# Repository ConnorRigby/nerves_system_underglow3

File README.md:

# ConeRGB Underglow3 Nerves Support

This is the base Nerves System configuration for [ConeRGB V3](https://github.com/connorrigby/underglow3).

| Feature              | Description                     |
| -------------------- | ------------------------------- |
| CPU                  | 1.2 GHz ARM Cortex-A7 Dual-Core |
| Memory               | 128 MB DDR3                     |
| Storage              | MicroSD                         |
| Linux kernel         | 6.1 w/ patches                  |
| IEx terminal         | UART `ttyS0`                    |
| GPIO, I2C, SPI       | Yes - [Elixir Circuits](https://github.com/elixir-circuits) |
| Display              | No                              |
| ADC                  | No                              |
| PWM                  | 8 channels                      |
| UART                 | ttyS0                           |
| Camera               | No                              |
| Ethernet             | No                              |
| WiFi                 | Onboard WiFi                    |
| RTC                  | No                              |
| HW Watchdog          | Yes                             |

## Special Thanks

Most of the hard work in this repo was gleamed from [YuzukiSBC](https://github.com/YuzukiHD/Buildroot-YuzukiSBC)

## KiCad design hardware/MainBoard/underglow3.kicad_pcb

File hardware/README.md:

# v0.1.0 RELEASE

This directory contains a tagged version of the "real" hardware repo. 
Everything in this directory should be considered for reference only and not used as source directly.

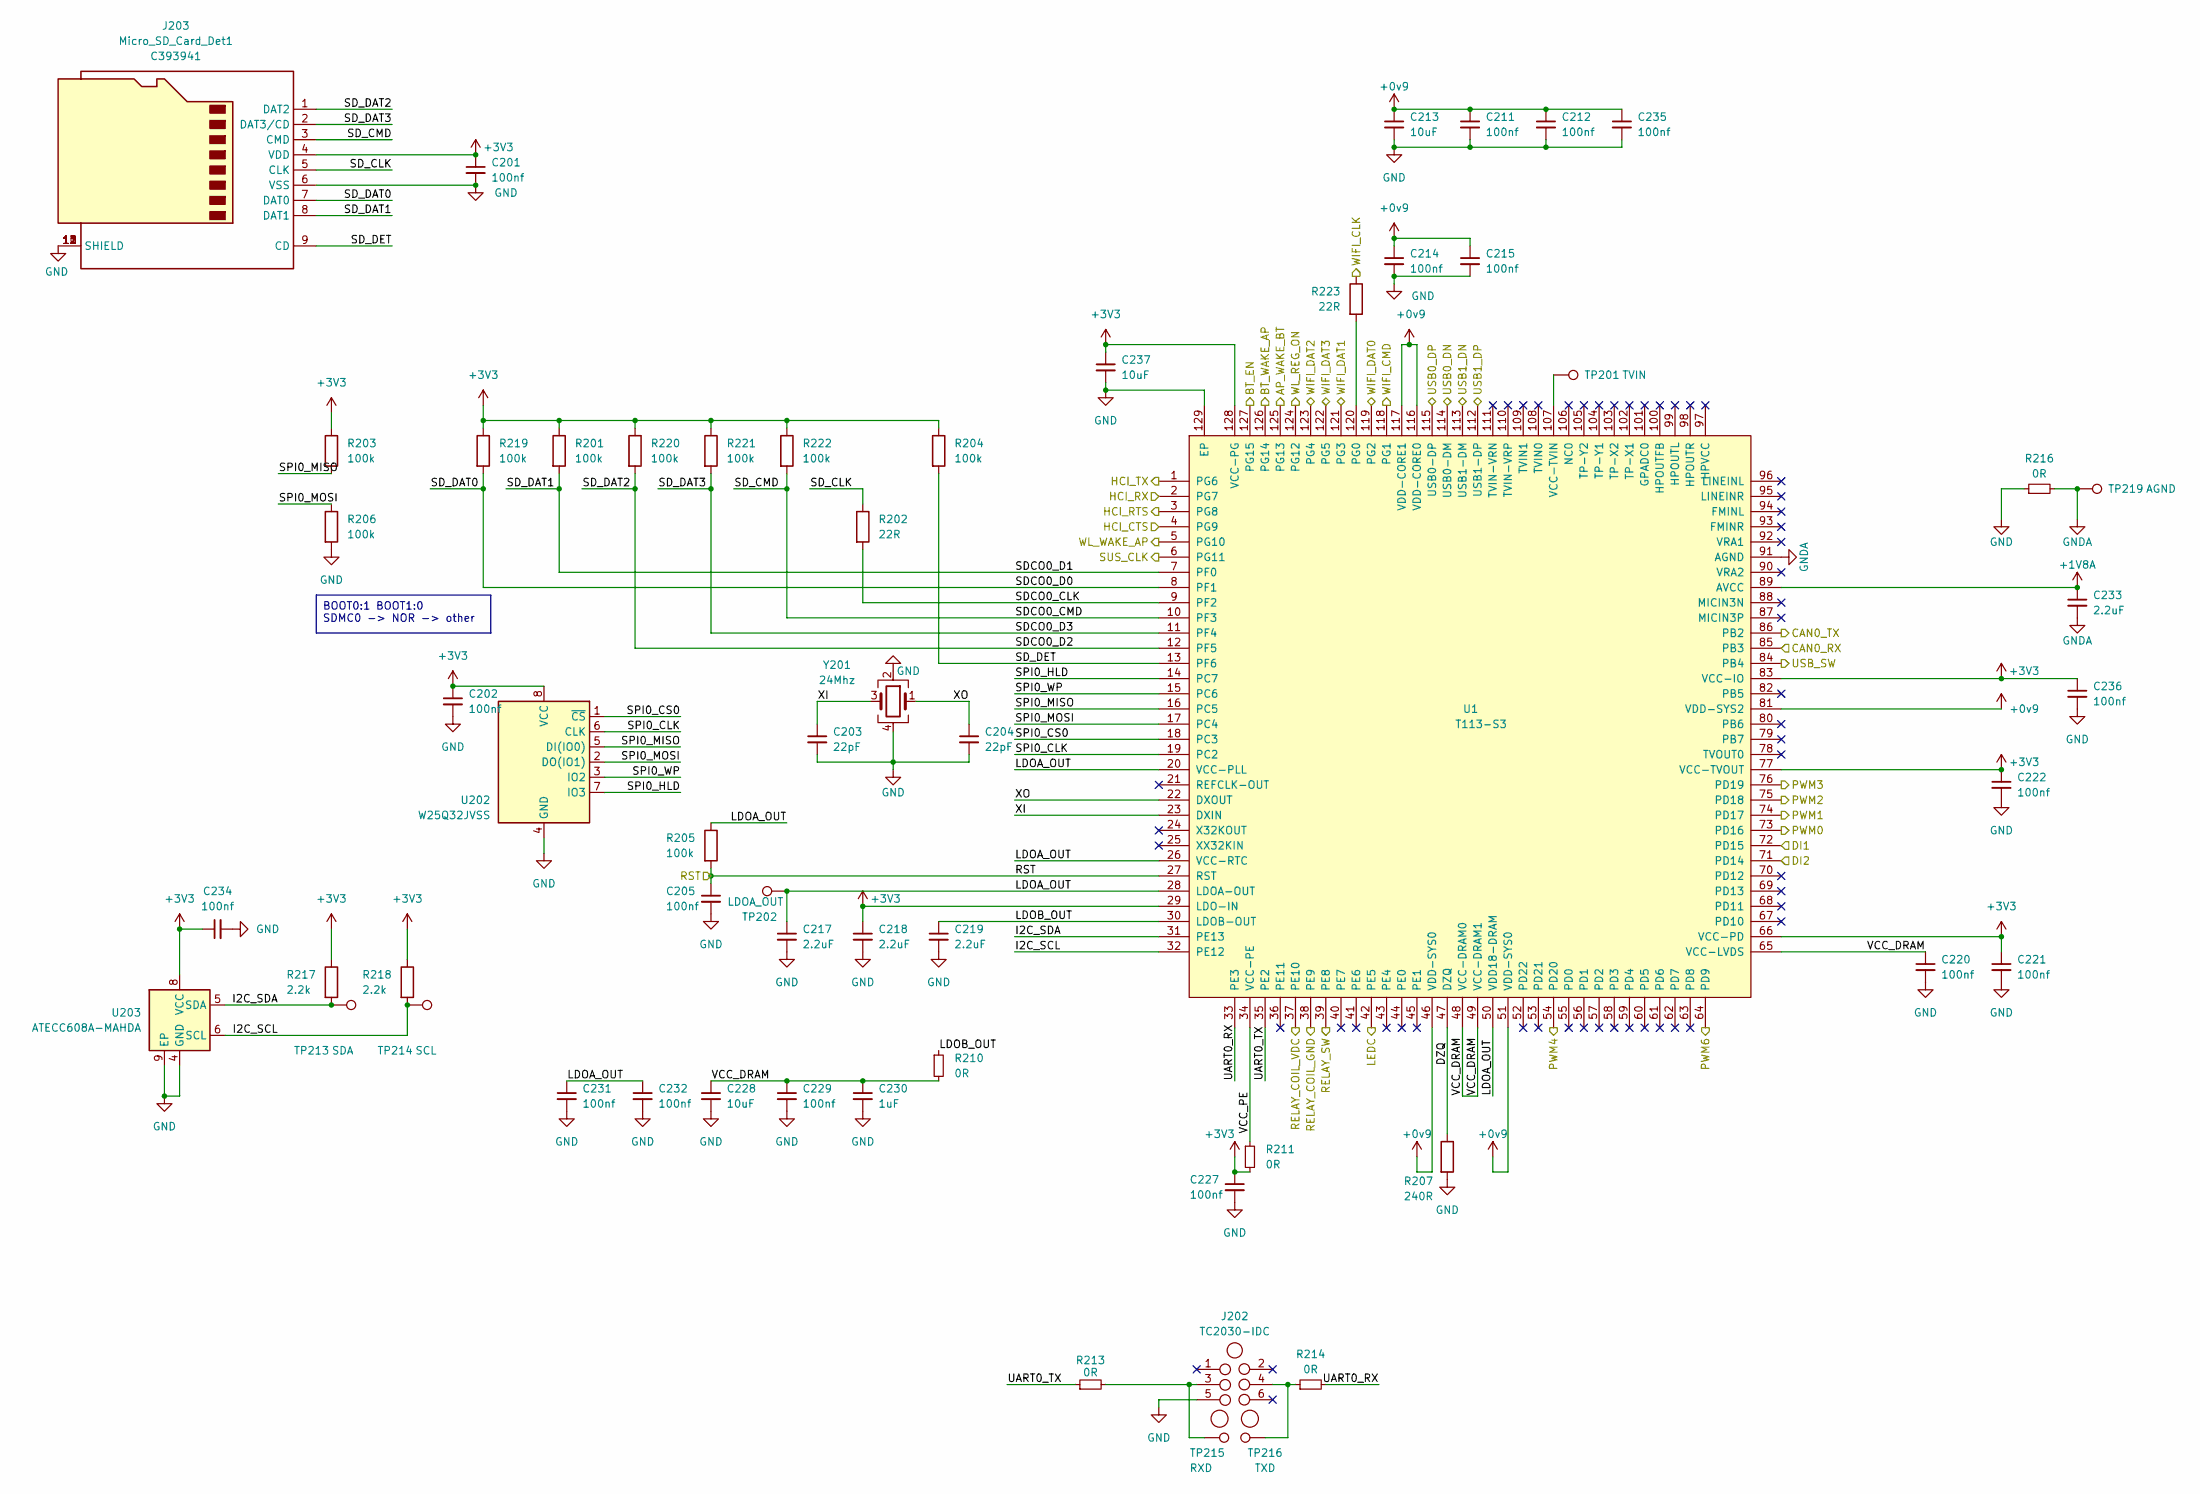
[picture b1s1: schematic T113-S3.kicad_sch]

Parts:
C201, C202, C205, C211, C212, C214, C215, C220, C221, C222, C227, C229, C231, C232, C234, C235, C236: 100nf; C_0402_1005Metric; MPN CL05B104KB54PNC; LCSC C307331
C203, C204: 22pF; C_0402_1005Metric; MPN 0402CG220J500NT; LCSC C1555
C213, C228, C237: 10uF; C_0603_1608Metric; MPN CL10A106MA8NRNC; LCSC C96446
C217, C218, C219, C233: 2.2uF; R_0402_1005Metric; MPN CL05A225MQ5NSNC; LCSC C12530
C230: 1uF; R_0402_1005Metric; MPN CL05A105KA5NQNC; LCSC C52923
J202: TC2030-IDC; Tag-Connect_TC2030-IDC-NL_2x03_P1.27mm_Vertical
J203: Micro_SD_Card_Det1; TF-SMD_TF-PUSH; MPN TF PUSH; LCSC C393941
R201, R203, R204, R205, R206, R219, R220, R221, R222: 100k; R_0402_1005Metric; MPN 0402WGF1003TCE; LCSC C25741
R202, R223: 22R; R_0402_1005Metric; MPN 0402WGF220JTCE; LCSC C25092
R207: 240R; R_0402_1005Metric; MPN 0402WGF2400TCE; LCSC C25094
R210, R211, R213, R214, R216: 0R; R_0402_1005Metric; MPN 0402WGF0000TCE; LCSC C17168
R217, R218: 2.2k; R_0402_1005Metric; MPN 0603WAF2201T5E; LCSC C4190
TP201: TVIN; TestPoint_Pad_D1.0mm
TP202: LDOA_OUT; TestPoint_Pad_D1.0mm
TP213: SDA; TestPoint_Pad_D1.0mm
TP214: SCL; TestPoint_Pad_D1.0mm
TP215: RXD; TestPoint_Pad_D1.0mm
TP216: TXD; TestPoint_Pad_D1.0mm
TP219: AGND; TestPoint_Pad_D1.0mm
U1: T113-S3; LQFP-128_L14.0-W14.0-P0.40-LS16.0-BL-EP5.6; MPN T113-S3; LCSC C5197687
U202: W25Q32JVSS; SOIC-8_5.23x5.23mm_P1.27mm; MPN W25Q32JVSSIQ; LCSC C179173
U203: ATECC608A-MAHDA; DFN-8-1EP_3x2mm_P0.5mm_EP1.3x1.5mm; MPN ATECC608A-MAHDA-S; LCSC C616908
Y201: 24Mhz; Crystal_SMD_3225-4Pin_3.2x2.5mm; MPN 3TJ424000XYFBC; LCSC C2149059

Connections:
+0v9: C211.1, C212.1, C213.1, C214.1, C215.1, C235.1; also elsewhere on the board
+1V8A: C233.1; also elsewhere on the board
+3V3: C201.1, C202.1, C218.1, C221.1, C222.1, C227.1, C234.1, C236.1, C237.1, J203.4 (VDD), R201.1, R203.1, R204.1, R211.2, R217.1, R218.1, R219.1, R220.1, R221.1, R222.1, U202.8 (VCC), U203.8 (VCC); also elsewhere on the board
/Application/DZQ: R207.1; also elsewhere on the board
/Application/I2C_SCL: R218.2, TP214.1, U203.6 (SCL); also elsewhere on the board
/Application/I2C_SDA: R217.2, TP213.1, U203.5 (SDA); also elsewhere on the board
/Application/LDOA_OUT: C217.1, C231.1, C232.1, R205.1, TP202.1; also elsewhere on the board
/Application/LDOB_OUT: C219.1, R210.1; also elsewhere on the board
/Application/RST: C205.1, R205.2; also elsewhere on the board
/Application/SDCO0_CLK: R202.2; also elsewhere on the board
/Application/SDCO0_CMD: J203.3 (CMD), R222.2; also elsewhere on the board
/Application/SDCO0_D0: J203.7 (DAT0), R219.2; also elsewhere on the board
/Application/SDCO0_D1: J203.8 (DAT1), R201.2; also elsewhere on the board
/Application/SDCO0_D2: J203.1 (DAT2), R220.2; also elsewhere on the board
/Application/SDCO0_D3: J203.2 (DAT3/CD), R221.2; also elsewhere on the board
/Application/SD_CLK: J203.5 (CLK), R202.1
/Application/SD_DET: J203.9 (CD), R204.2; also elsewhere on the board
/Application/SPI0_CLK: U202.6 (CLK); also elsewhere on the board
/Application/SPI0_CS0: U202.1 (~CS); also elsewhere on the board
/Application/SPI0_HLD: U202.7 (IO3); also elsewhere on the board
/Application/SPI0_MISO: R203.2, U202.5 (DI(IO0)); also elsewhere on the board
/Application/SPI0_MOSI: R206.1, U202.2 (DO(IO1)); also elsewhere on the board
/Application/SPI0_WP: U202.3 (IO2); also elsewhere on the board
/Application/UART0_RX: R214.2; also elsewhere on the board
/Application/UART0_TX: R213.1; also elsewhere on the board
/Application/VCC_DRAM: C220.1, C228.1, C229.1, C230.1, R210.2; also elsewhere on the board
/Application/VCC_PE: R211.1; also elsewhere on the board
/Application/WIFI_CLK: R223.1; also elsewhere on the board
/Application/XI: C203.1, Y201.3; also elsewhere on the board
/Application/XO: C204.1, Y201.1; also elsewhere on the board
GND: C201.2, C202.2, C203.2, C204.2, C205.2, C211.2, C212.2, C213.2, C214.2, C215.2, C217.2, C218.2, C219.2, C220.2, C221.2, C222.2, C227.2, C228.2, C229.2, C230.2, C231.2, C232.2, C234.2, C235.2, C236.2, C237.2, J202.5, J203.6 (VSS), J203.10 (SHIELD), J203.11 (SHIELD), J203.12 (SHIELD), J203.13 (SHIELD), R206.2, R207.2, R216.1, U202.4 (GND), U203.4 (GND), U203.9 (EP), Y201.2, Y201.4; also elsewhere on the board
GNDA: C233.2, R216.2, TP219.1; also elsewhere on the board
unnamed: J202.3, R213.2, TP215.1
unnamed: J202.4, R214.1, TP216.1
unnamed 127: R223.2; also elsewhere on the board
unnamed 128: TP201.1; also elsewhere on the board

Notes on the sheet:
BOOT0:1 BOOT1:0 SDMC0 -> NOR -> other

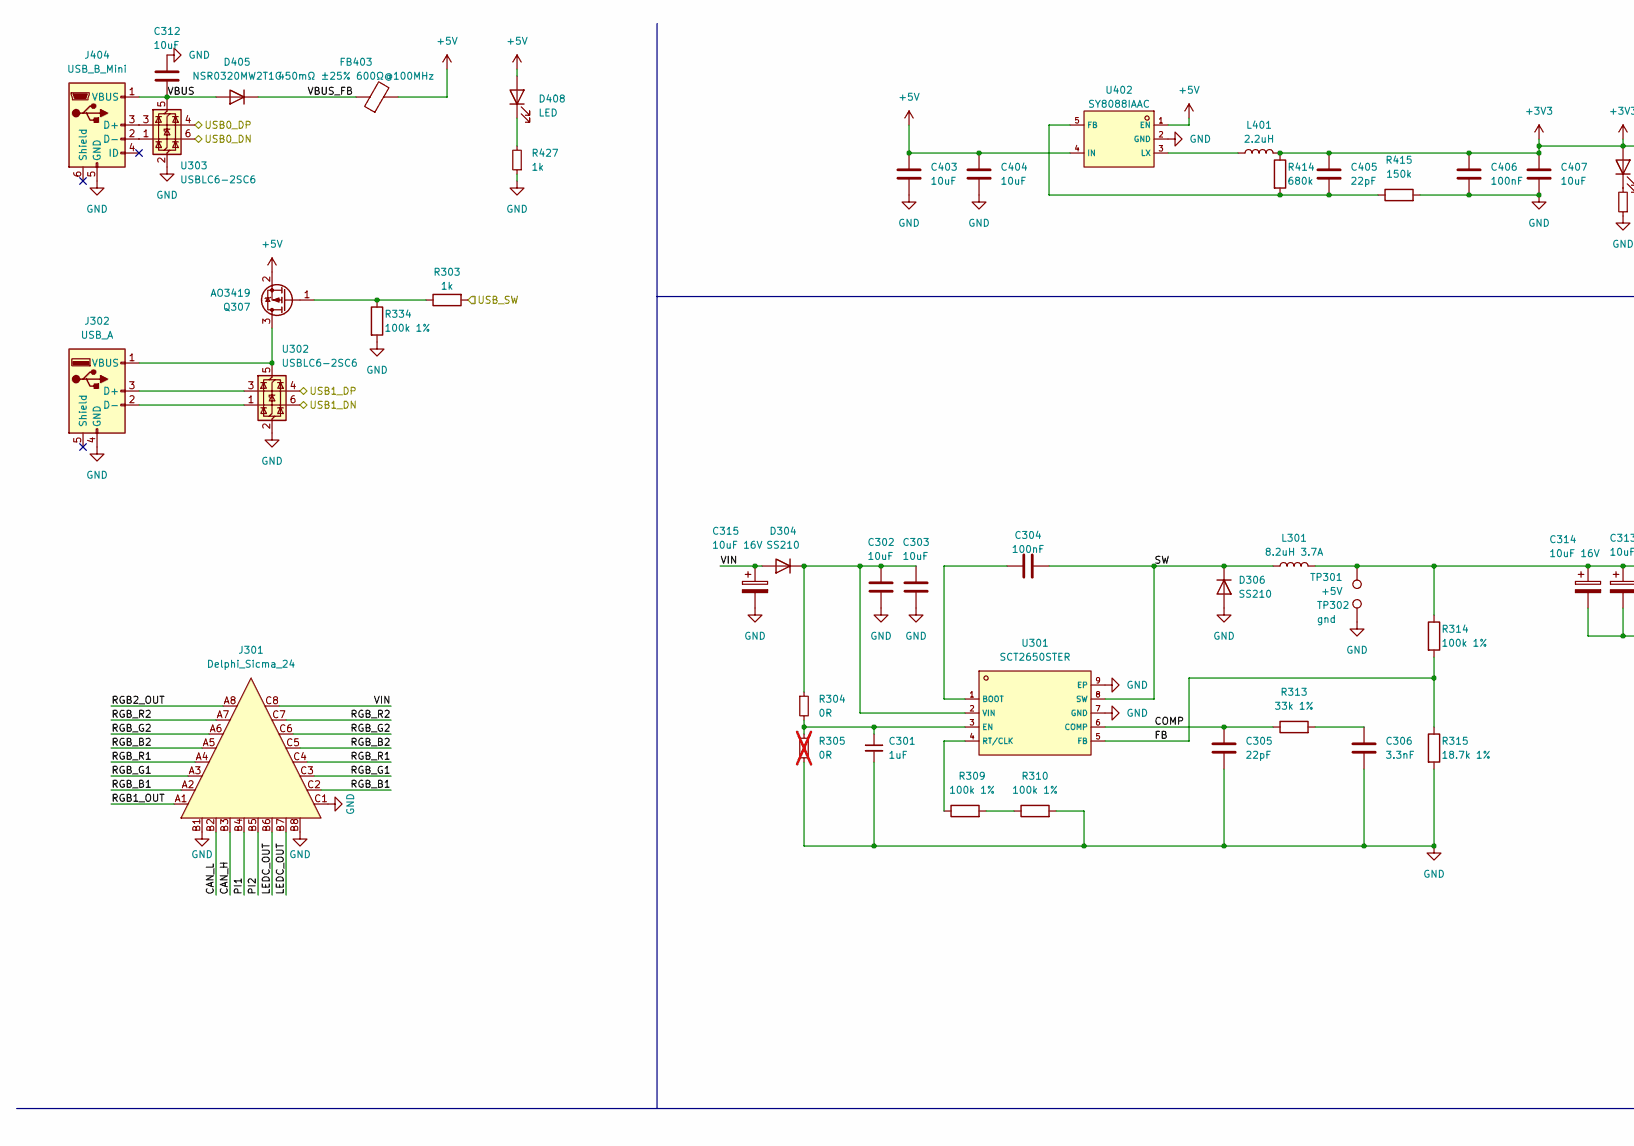
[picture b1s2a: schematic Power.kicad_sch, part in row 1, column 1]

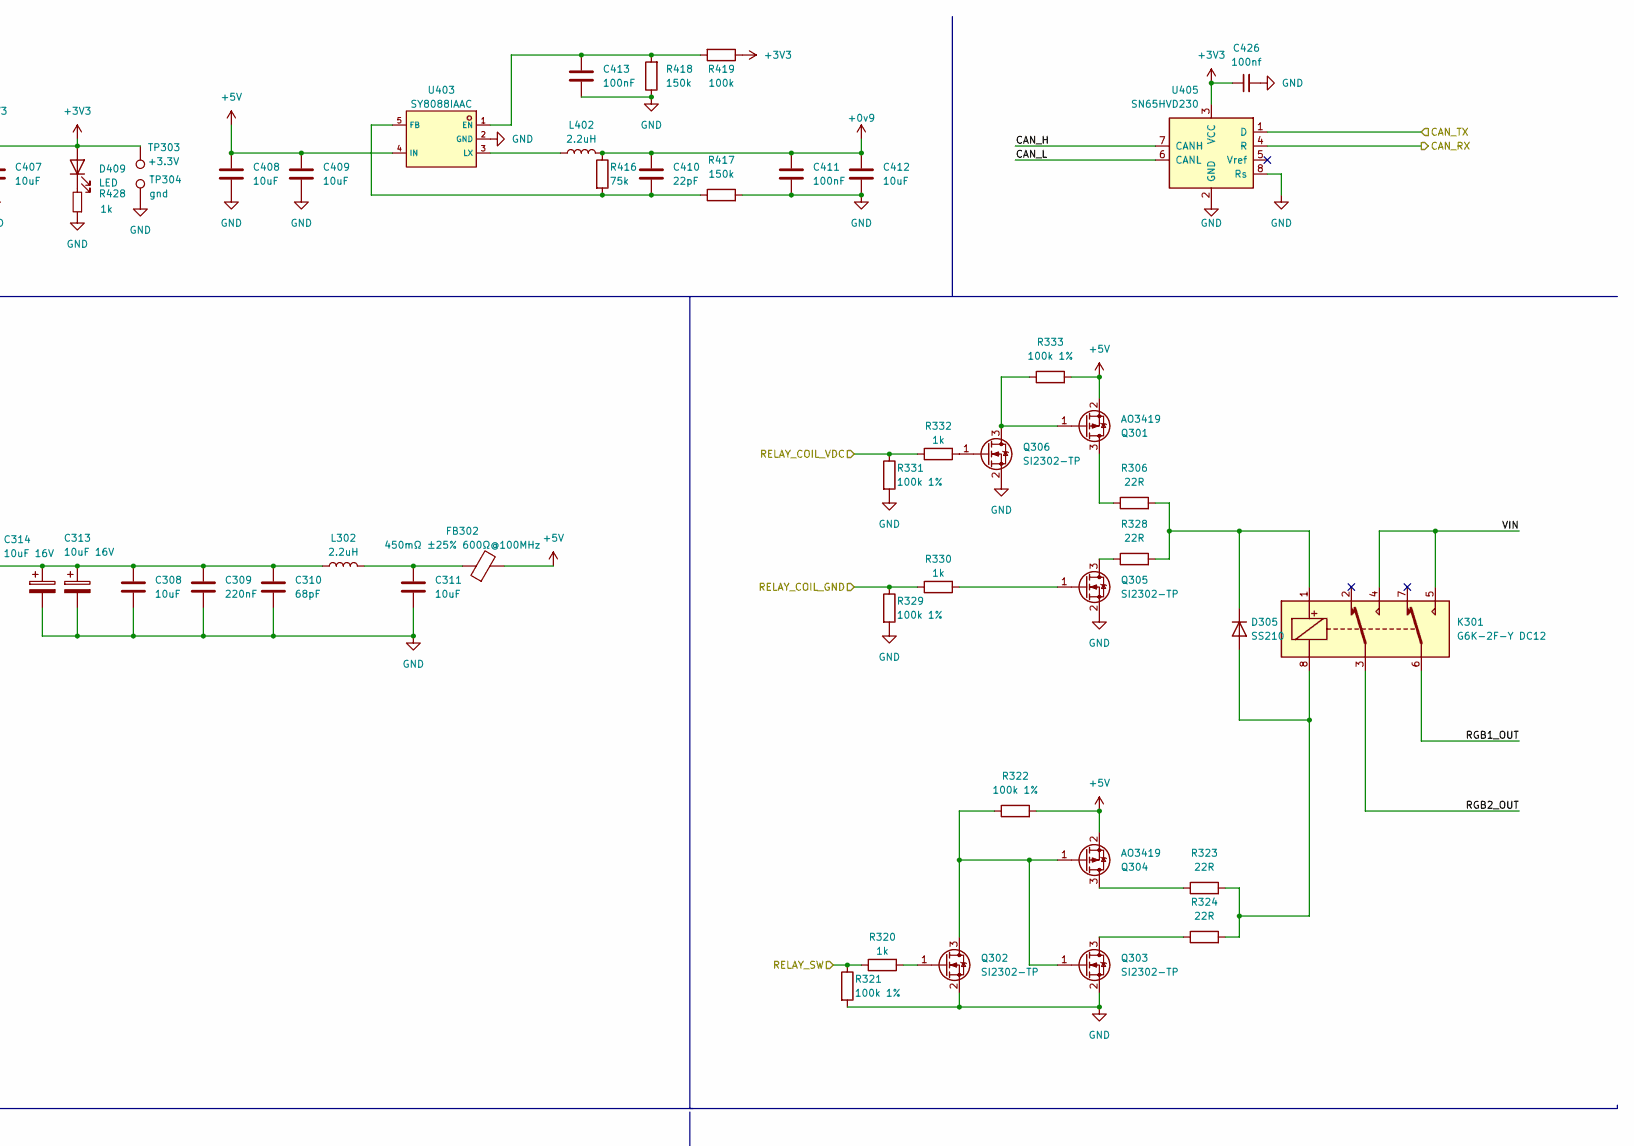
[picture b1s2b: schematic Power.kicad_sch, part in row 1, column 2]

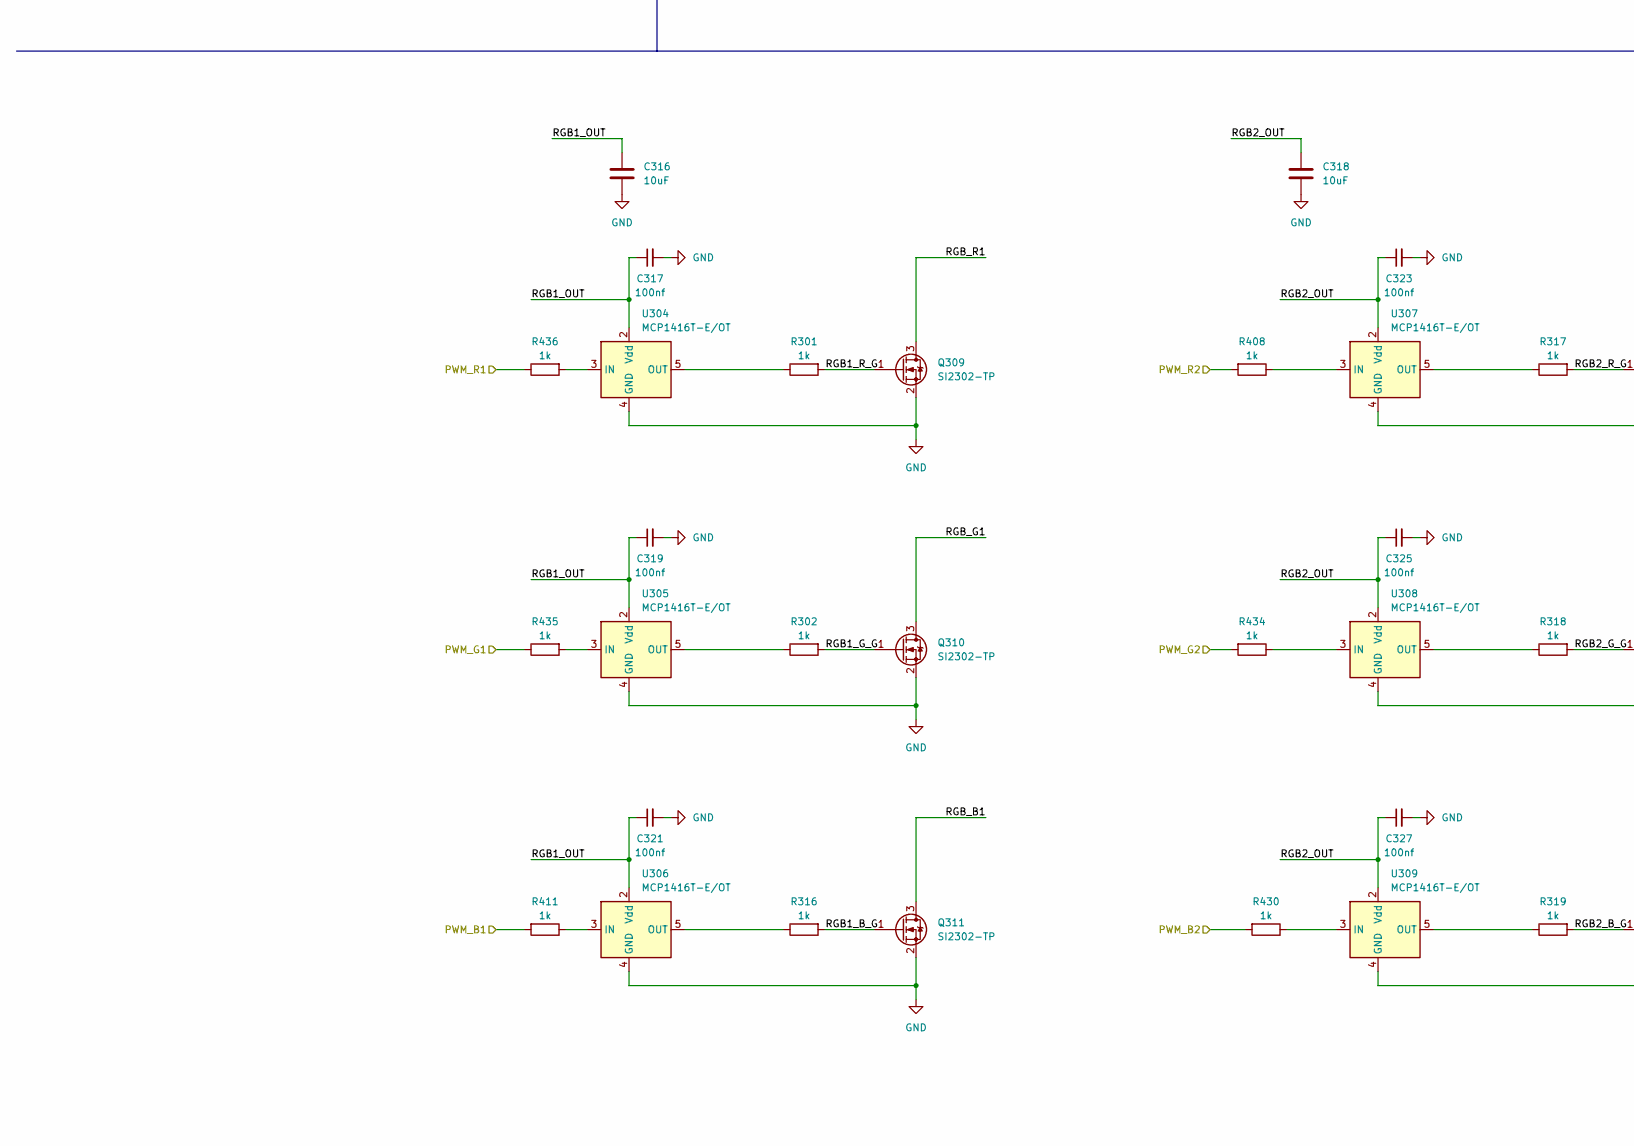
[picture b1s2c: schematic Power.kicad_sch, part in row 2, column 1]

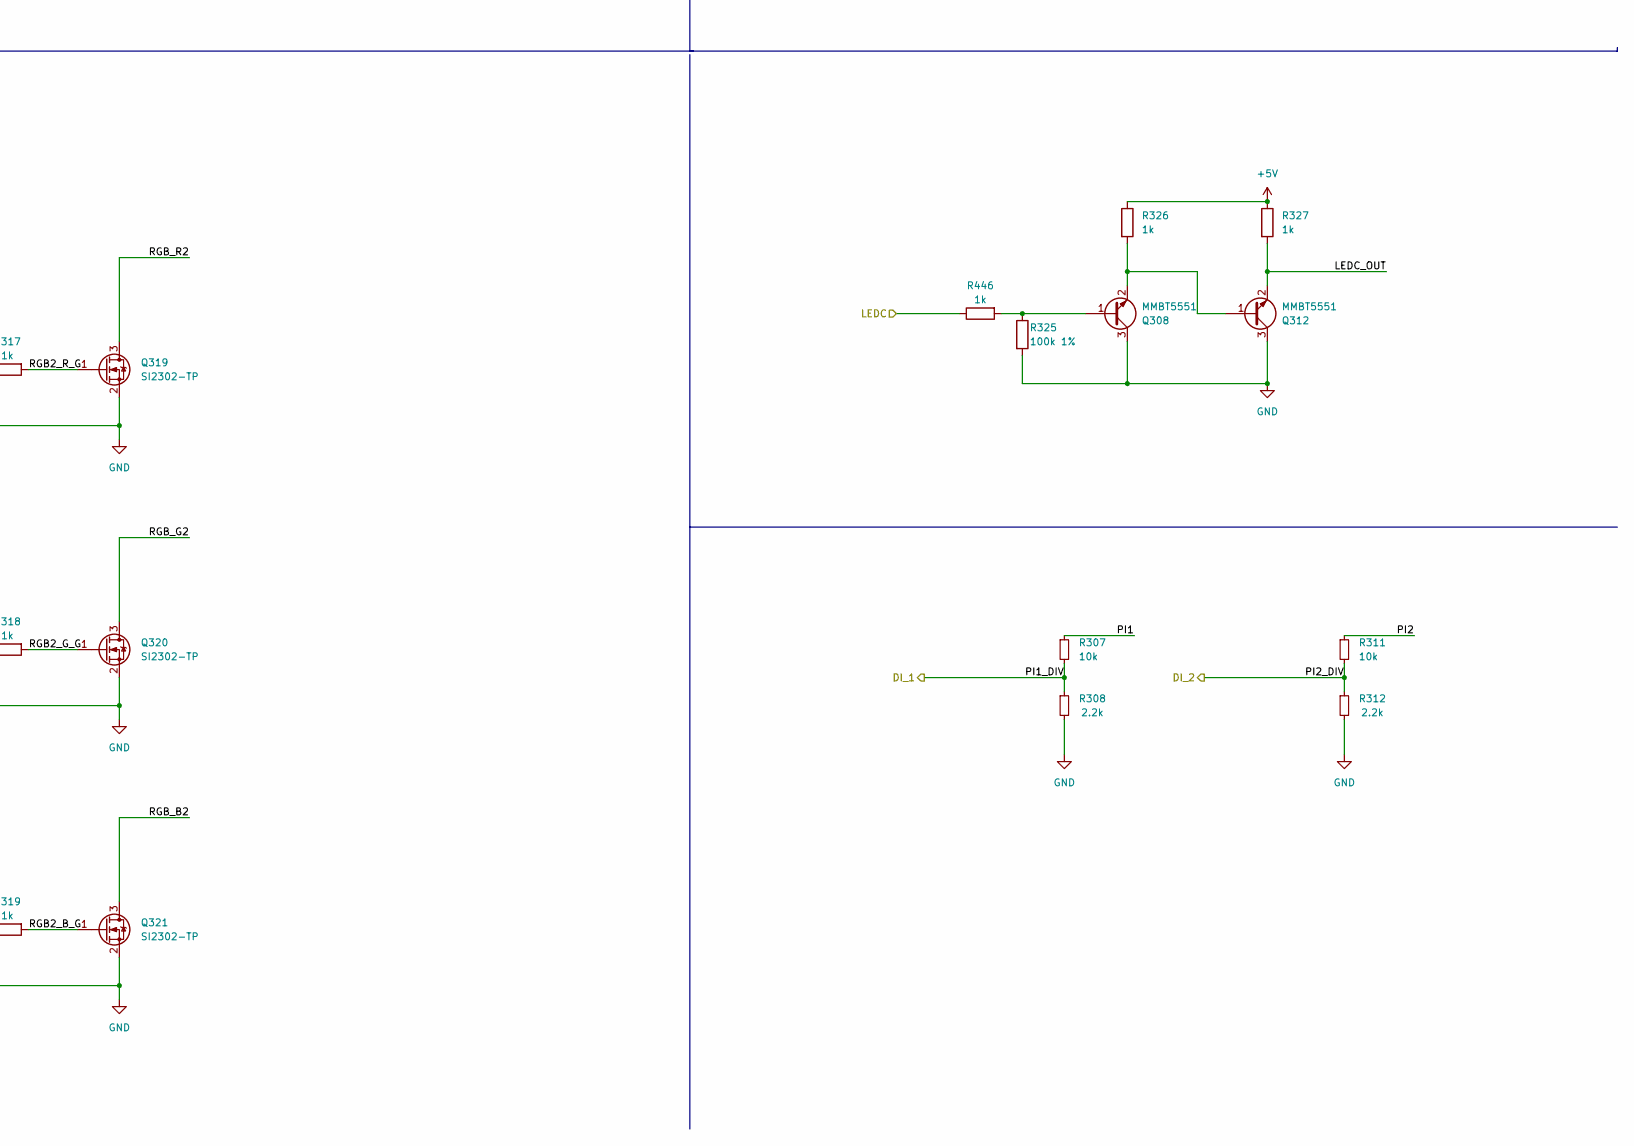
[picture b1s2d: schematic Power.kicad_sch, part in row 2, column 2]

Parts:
C301: 1uF; R_0402_1005Metric; MPN CL05A105KA5NQNC; LCSC C52923
C302, C303, C308, C311, C312: 10uF; C_0603_1608Metric; MPN CL10A106MA8NRNC; LCSC C96446
C304, C406, C411, C413: 100nF; C_0402_1005Metric; MPN CL05B104KB54PNC; LCSC C307331
C305, C405, C410: 22pF; C_0402_1005Metric; MPN 0402CG220J500NT; LCSC C1555
C306: 3.3nF; C_0402_1005Metric; MPN CL05B332KB5NNNC; LCSC C26404
C309: 220nF; C_0603_1608Metric; MPN CL10B224KA8NNNC; LCSC C21120
C310: 68pF; C_0603_1608Metric; MPN CL10C680JB8NNNC; LCSC C28262
C313, C314, C315: 10uF 16V; CP_EIA-3216-18_Kemet-A; MPN TAJA106K016RNJ; LCSC C7171
C316, C318, C403, C404, C407, C408, C409, C412: 10uF; C_0603_1608Metric; MPN C0603X5R106M100NT; LCSC C466780
C317, C319, C321, C323, C325, C327, C426: 100nf; C_0402_1005Metric; MPN CL05B104KB54PNC; LCSC C307331
D304, D305, D306: SS210; D_SMA; MPN SS210; LCSC C14996
D405: NSR0320MW2T1G; D_SOD-323; MPN 1N5819WS; LCSC C191023
D408, D409: LED; LED_0402_1005Metric; MPN LTST-C281KRKT; LCSC C364556
FB302, FB403: 450mΩ ±25% 600Ω@100MHz; L_0603_1608Metric; MPN GZ1608D601TF; LCSC C1002
J301: Delphi_Sicma_24; Delphi_Sicma_24_Black
J302: USB_A; USB-A-SMD_USB-234-BCW; MPN USB-234-BCW; LCSC C720528
J404: USB_B_Mini; USB_Mini-B_Lumberg_2486_01_Horizontal; MPN UX-144S-ACP5; LCSC C720611
K301: G6K-2F-Y DC12; Relay_DPDT_Omron_G6K-2F-Y; MPN G6K-2F-Y DC12; LCSC C397194
L301: 8.2uH 3.7A; IND-SMD_L7.0-W6.6_FXL0630; MPN SLO0624H8R2MTT; LCSC C325977
L302: 2.2uH; L_0603_1608Metric; MPN 0402WGF0000TCE; LCSC C17168
L401, L402: 2.2uH; IND-SMD_L2.0-W1.6_VLS201610CX-150M; MPN WPN201610H2R2MT; LCSC C97005
Q301, Q304, Q307: AO3419; SOT-23W; MPN AO3419; LCSC C88053
Q302, Q303, Q305, Q306: SI2302-TP; SOT-23; MPN SI2302-TP; LCSC C77977
Q308, Q312: MMBT5551; SOT-23; MPN MMBT5551; LCSC C2145
Q309, Q310, Q311, Q319, Q320, Q321: SI2302-TP; SOT-23-3; MPN AO3400A; LCSC C20917
R301, R302, R303, R316, R317, R318, R319, R320, R326, R327, R330, R332, R408, R411, R427, R428, R430, R434, R435, R436, R446: 1k; R_0402_1005Metric; MPN 0402WGF1001TCE; LCSC C11702
R304: 0R; R_0402_1005Metric; MPN 0402WGF0000TCE; LCSC C17168
R305: 0R; R_0402_1005Metric; MPN 0402WGF0000TCE; LCSC C17168; not fitted
R306, R323, R324, R328: 22R; R_0402_1005Metric; MPN 0402WGF220JTCE; LCSC C25092
R307, R311: 10k; R_0603_1608Metric; MPN 0603WAF1002T5E; LCSC C25804
R308, R312: 2.2k; R_0603_1608Metric; MPN 0603WAF2201T5E; LCSC C4190
R309, R310, R314, R321, R322, R325, R329, R331, R333, R334: 100k 1%; R_0402_1005Metric; MPN 0402WGF1003TCE; LCSC C25741
R313: 33k 1%; R_0402_1005Metric; MPN 0402WGF3302TCE; LCSC C25779
R315: 18.7k 1%; R_0402_1005Metric; MPN 0402WGF1872TCE; LCSC C11476
R414: 680k; R_0402_1005Metric; MPN 0402WGF6803TCE; LCSC C4131
R415, R417, R418: 150k; R_0402_1005Metric; MPN 0402WGF1503TCE; LCSC C25755
R416: 75k; R_0402_1005Metric; MPN 0402WGF7502TCE; LCSC C25798
R419: 100k; R_0402_1005Metric; MPN 0402WGF1003TCE; LCSC C25741
TP301: +5V; TestPoint_Pad_D1.0mm
TP302, TP304: gnd; TestPoint_Pad_D1.0mm
TP303: +3.3V; TestPoint_Pad_D1.0mm
U301: SCT2650STER; HSOP-8-1EP_3.9x4.9mm_P1.27mm_EP2.41x3.1mm; MPN SCT2650STER; LCSC C2840771
U302, U303: USBLC6-2SC6; SOT-23-6; MPN USBLC6-2SC6; LCSC C2827654
U304, U305, U306, U307, U308, U309: MCP1416T-E/OT; SOT-23-5; LCSC C83775
U402, U403: SY8088IAAC; SOT-23-5; MPN SY8088IAAC; LCSC C479072
U405: SN65HVD230; SOIC-8_3.9x4.9mm_P1.27mm; MPN SN65HVD230DR; LCSC C12084

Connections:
+0v9: C410.1, C411.1, C412.1, L402.2, R416.1; also elsewhere on the board
+3V3: C405.1, C406.1, C407.1, C426.1, D409.2 (A), L401.2, R414.1, R419.1, TP303.1, U405.3 (VCC); also elsewhere on the board
+5V: C403.1, C404.1, C408.1, C409.1, D408.2 (A), FB302.2, FB403.2, Q301.2 (S), Q304.2 (S), Q307.2 (S), R322.2, R326.1, R327.1, R333.2, U402.1 (EN), U402.4 (IN), U403.4 (IN)
/Application/CAN0_RX: U405.4 (R); also elsewhere on the board
/Application/CAN0_TX: U405.1 (D); also elsewhere on the board
/Application/LEDC: R446.1; also elsewhere on the board
/Application/PWM0: R430.2; also elsewhere on the board
/Application/PWM1: R436.1; also elsewhere on the board
/Application/PWM2: R435.1; also elsewhere on the board
/Application/PWM3: R411.2; also elsewhere on the board
/Application/PWM4: R408.2; also elsewhere on the board
/Application/PWM6: R434.2; also elsewhere on the board
/Application/RELAY_COIL_GND: R329.1, R330.1; also elsewhere on the board
/Application/RELAY_COIL_VDC: R331.1, R332.1; also elsewhere on the board
/Application/RELAY_SW: R320.1, R321.1; also elsewhere on the board
/Application/USB0_DN: U303.6 (I/O1); also elsewhere on the board
/Application/USB0_DP: U303.4 (I/O2); also elsewhere on the board
/Application/USB1_DN: U302.6 (I/O1); also elsewhere on the board
/Application/USB1_DP: U302.4 (I/O2); also elsewhere on the board
/Application/USB_SW: R303.2; also elsewhere on the board
/Power/CAN_H: J301.B3, U405.7 (CANH)
/Power/CAN_L: J301.B2, U405.6 (CANL)
/Power/COMP: C305.1, R313.1, U301.6 (COMP)
/Power/FB: R314.2, R315.1, U301.5 (FB)
/Power/LEDC_OUT: J301.B6, J301.B7, Q312.2 (E), R327.2
/Power/PI1: J301.B4, R307.1
/Power/PI1_DIV: R307.2, R308.1; also elsewhere on the board
/Power/PI2: J301.B5, R311.1
/Power/PI2_DIV: R311.2, R312.1; also elsewhere on the board
/Power/RGB1_B_G: Q311.1 (G), R316.2
/Power/RGB1_G_G: Q310.1 (G), R302.2
/Power/RGB1_OUT: C316.1, C317.1, C319.1, C321.1, J301.A1, K301.6, U304.2 (Vdd), U305.2 (Vdd), U306.2 (Vdd)
/Power/RGB1_R_G: Q309.1 (G), R301.2
/Power/RGB2_B_G: Q321.1 (G), R319.2
/Power/RGB2_G_G: Q320.1 (G), R318.2
/Power/RGB2_OUT: C318.1, C323.1, C325.1, C327.1, J301.A8, K301.3, U307.2 (Vdd), U308.2 (Vdd), U309.2 (Vdd)
/Power/RGB2_R_G: Q319.1 (G), R317.2
/Power/RGB_B1: J301.A2, J301.C2, Q311.3 (D)
/Power/RGB_B2: J301.A5, J301.C5, Q321.3 (D)
/Power/RGB_G1: J301.A3, J301.C3, Q310.3 (D)
/Power/RGB_G2: J301.A6, J301.C6, Q320.3 (D)
/Power/RGB_R1: J301.A4, J301.C4, Q309.3 (D)
/Power/RGB_R2: J301.A7, J301.C7, Q319.3 (D)
/Power/SW: C304.2, D306.1 (K), L301.1, U301.8 (SW)
/Power/VBUS: C312.2, D405.2 (A), J404.1 (VBUS), U303.5 (VBUS)
/Power/VBUS_FB: D405.1 (K), FB403.1
/Power/VIN: C315.1, D304.2 (A), J301.C8, K301.4, K301.5
GND: C301.2, C302.2, C303.2, C305.2, C306.2, C308.2, C309.2, C310.2, C311.2, C312.1, C313.2, C314.2, C315.2, C316.2, C317.2, C318.2, C319.2, C321.2, C323.2, C325.2, C327.2, C403.2, C404.2, C406.2, C407.2, C408.2, C409.2, C411.2, C412.2, C413.2, C426.2, D306.2 (A), J301.B1, J301.B8, J301.C1, J302.4 (GND), J404.5 (GND), Q302.2 (S), Q303.2 (S), Q305.2 (S), Q306.2 (S), Q308.3 (C), Q309.2 (S), Q310.2 (S), Q311.2 (S), Q312.3 (C), Q319.2 (S), Q320.2 (S), Q321.2 (S), R305.2, R308.2, R310.2, R312.2, R315.2, R321.2, R325.2, R329.2, R331.2, R334.2, R415.2, R417.2, R418.1, R427.1, R428.1, TP302.1, TP304.1, U301.7 (GND), U301.9 (EP), U302.2 (GND), U303.2 (GND), U304.4 (GND), U305.4 (GND), U306.4 (GND), U307.4 (GND), U308.4 (GND), U309.4 (GND), U402.2 (GND), U403.2 (GND), U405.2 (GND), U405.8 (Rs); also elsewhere on the board
unnamed: C306.1, R313.2
unnamed: C308.1, C309.1, C310.1, C313.1, C314.1, L301.2, L302.1, R314.1, TP301.1
unnamed: C311.1, FB302.1, L302.2
unnamed: C302.1, C303.1, D304.1 (K), R304.1, U301.2 (VIN)
unnamed: D305.2 (A), K301.8, R323.2, R324.2
unnamed: D305.1 (K), K301.1, R306.2, R328.2
unnamed: D408.1 (K), R427.2
unnamed: D409.1 (K), R428.2
unnamed: J302.3 (D+), U302.3 (I/O2)
unnamed: J302.2 (D-), U302.1 (I/O1)
unnamed: J302.1 (VBUS), Q307.3 (D), U302.5 (VBUS)
unnamed: J404.3 (D+), U303.3 (I/O2)
unnamed: J404.2 (D-), U303.1 (I/O1)
unnamed: Q301.3 (D), R306.1
unnamed: Q301.1 (G), Q306.3 (D), R333.1
unnamed: Q302.3 (D), Q303.1 (G), Q304.1 (G), R322.1
unnamed: Q302.1 (G), R320.2
unnamed: Q303.3 (D), R324.1
unnamed: Q304.3 (D), R323.1
unnamed: Q305.3 (D), R328.1
unnamed: Q305.1 (G), R330.2
unnamed: Q306.1 (G), R332.2
unnamed: Q307.1 (G), R303.1, R334.1
unnamed: Q308.1 (B), R325.1, R446.2
unnamed: Q308.2 (E), Q312.1 (B), R326.2
unnamed: R309.2, R310.1
unnamed: C304.1, U301.1 (BOOT)
unnamed: C301.1, R304.2, R305.1, U301.3 (EN)
unnamed: R309.1, U301.4 (RT/CLK)
unnamed: R436.2, U304.3 (IN)
unnamed: R301.1, U304.5 (OUT)
unnamed: R435.2, U305.3 (IN)
unnamed: R302.1, U305.5 (OUT)
unnamed: R411.1, U306.3 (IN)
unnamed: R316.1, U306.5 (OUT)
unnamed: R408.1, U307.3 (IN)
unnamed: R317.1, U307.5 (OUT)
unnamed: R434.1, U308.3 (IN)
unnamed: R318.1, U308.5 (OUT)
unnamed: R430.1, U309.3 (IN)
unnamed: R319.1, U309.5 (OUT)
unnamed: C405.2, R414.2, R415.1, U402.5 (FB)
unnamed: L401.1, U402.3 (LX)
unnamed: C413.1, R418.2, R419.2, U403.1 (EN)
unnamed: C410.2, R416.2, R417.1, U403.5 (FB)
unnamed: L402.1, U403.3 (LX)

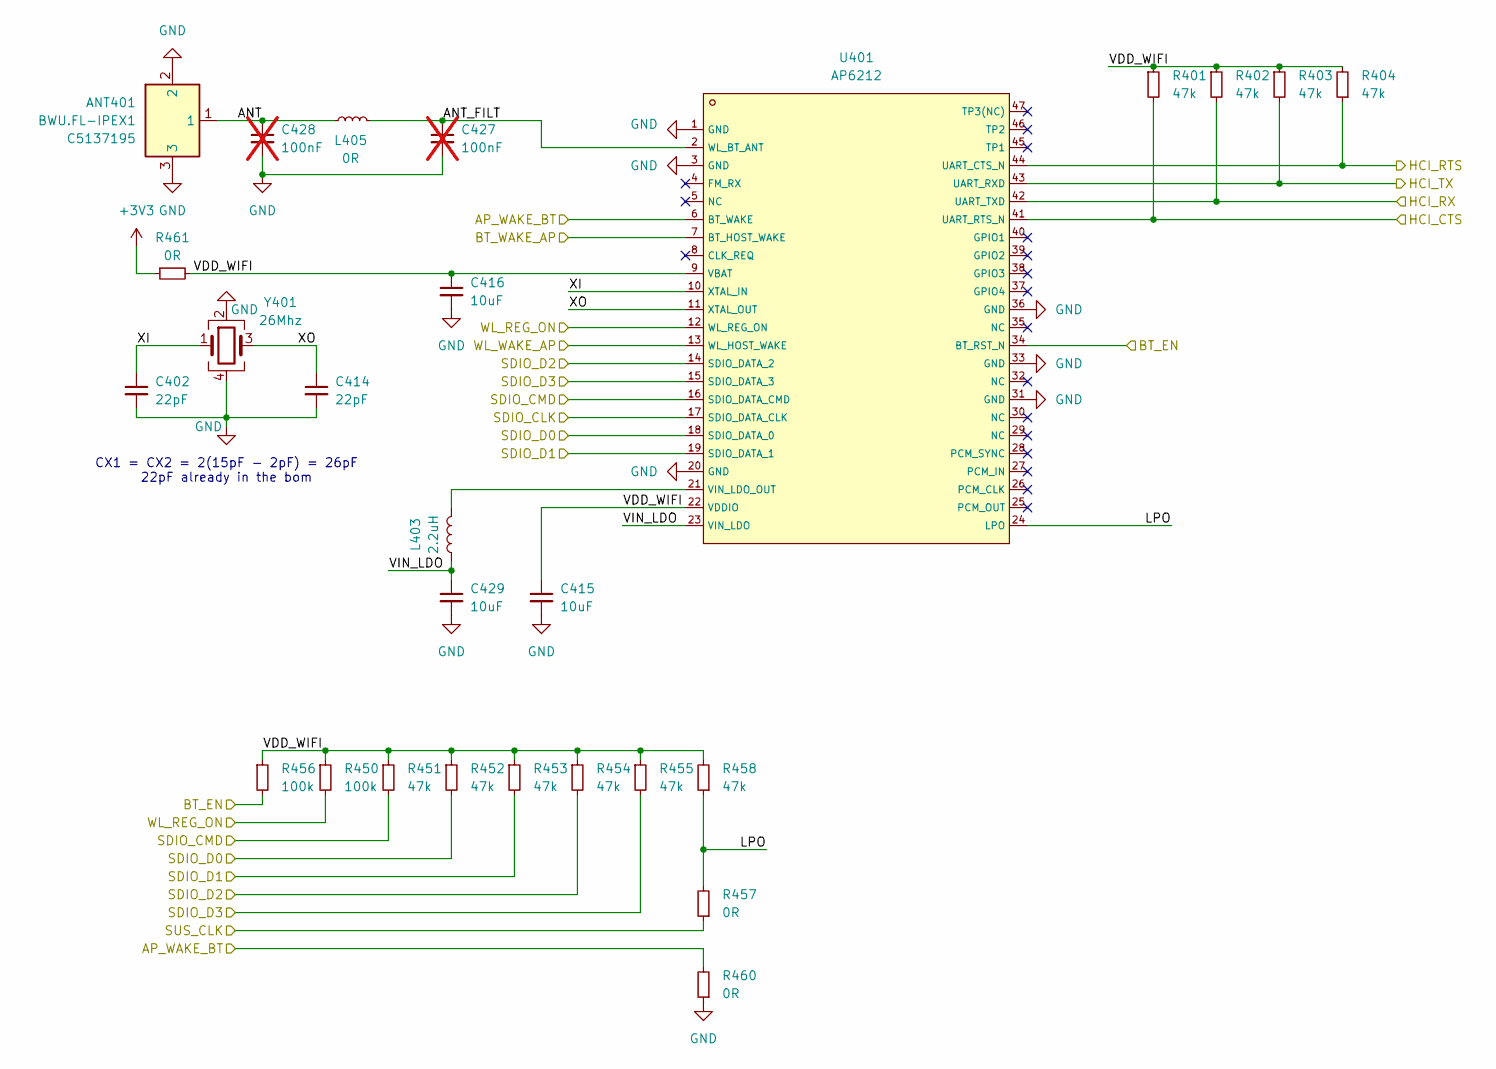
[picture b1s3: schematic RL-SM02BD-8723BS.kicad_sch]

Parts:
ANT401: BWU.FL-IPEX1; IPEX-SMD_BWIPX-1-001E; MPN BWU.FL-IPEX1; LCSC C5137195
C402, C414: 22pF; C_0402_1005Metric; MPN 0402CG220J500NT; LCSC C1555
C415, C416, C429: 10uF; C_0603_1608Metric; MPN CL10A106MA8NRNC; LCSC C96446
C427, C428: 100nF; R_0402_1005Metric; MPN CL05B104KB54PNC; LCSC C307331; not fitted
L403: 2.2uH; L_0603_1608Metric; MPN 0402WGF0000TCE; LCSC C17168
L405: 0R; R_0402_1005Metric; MPN 0402WGF0000TCE; LCSC C17168
R401, R402, R403, R404, R451, R452, R453, R454, R455, R458: 47k; R_0402_1005Metric; MPN 0402WGF4702TCE; LCSC C25792
R450, R456: 100k; R_0402_1005Metric; MPN 0402WGF1003TCE; LCSC C25741
R457, R460, R461: 0R; R_0402_1005Metric; MPN 0402WGF0000TCE; LCSC C17168
U401: AP6212; QFN-44_L12.0-W12.0-P0.90-TL_AP6212; LCSC C2798300
Y401: 26Mhz; Crystal_SMD_3225-4Pin_3.2x2.5mm; MPN TAXM26M4RHBCCT2T; LCSC C516065

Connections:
+3V3: R461.1; also elsewhere on the board
/Application/AP_WAKE_BT: R460.2, U401.6 (BT_WAKE); also elsewhere on the board
/Application/BT_EN: R456.2, U401.34 (BT_RST_N); also elsewhere on the board
/Application/BT_WAKE_AP: U401.7 (BT_HOST_WAKE); also elsewhere on the board
/Application/HCI_CTS: R404.1, U401.44 (UART_CTS_N); also elsewhere on the board
/Application/HCI_RTS: R401.2, U401.41 (UART_RTS_N); also elsewhere on the board
/Application/HCI_RX: R403.2, U401.43 (UART_RXD); also elsewhere on the board
/Application/HCI_TX: R402.2, U401.42 (UART_TXD); also elsewhere on the board
/Application/SUS_CLK: R457.1; also elsewhere on the board
/Application/WIFI_CLK: U401.17 (SDIO_DATA_CLK); also elsewhere on the board
/Application/WIFI_CMD: R451.2, U401.16 (SDIO_DATA_CMD); also elsewhere on the board
/Application/WIFI_DAT0: R452.2, U401.18 (SDIO_DATA_0); also elsewhere on the board
/Application/WIFI_DAT1: R453.2, U401.19 (SDIO_DATA_1); also elsewhere on the board
/Application/WIFI_DAT2: R454.2, U401.14 (SDIO_DATA_2); also elsewhere on the board
/Application/WIFI_DAT3: R455.2, U401.15 (SDIO_DATA_3); also elsewhere on the board
/Application/WL_REG_ON: R450.2, U401.12 (WL_REG_ON); also elsewhere on the board
/Application/WL_WAKE_AP: U401.13 (WL_HOST_WAKE); also elsewhere on the board
/RL-SM02BD-8723BS/ANT: ANT401.1, C428.1, L405.1
/RL-SM02BD-8723BS/ANT_FILT: C427.1, L405.2, U401.2 (WL_BT_ANT)
/RL-SM02BD-8723BS/LPO: R457.2, R458.1, U401.24 (LPO)
/RL-SM02BD-8723BS/VDD_WIFI: C415.1, C416.1, R401.1, R402.1, R403.1, R404.2, R450.1, R451.1, R452.1, R453.1, R454.1, R455.1, R456.1, R458.2, R461.2, U401.9 (VBAT), U401.22 (VDDIO)
/RL-SM02BD-8723BS/VIN_LDO: C429.1, L403.1, U401.23 (VIN_LDO)
/RL-SM02BD-8723BS/XI: C402.1, U401.10 (XTAL_IN), Y401.1
/RL-SM02BD-8723BS/XO: C414.1, U401.11 (XTAL_OUT), Y401.3
GND: ANT401.2, ANT401.3, C402.2, C414.2, C415.2, C416.2, C427.2, C428.2, C429.2, R460.1, U401.1 (GND), U401.3 (GND), U401.20 (GND), U401.31 (GND), U401.33 (GND), U401.36 (GND), Y401.2, Y401.4; also elsewhere on the board
unnamed: L403.2, U401.21 (VIN_LDO_OUT)

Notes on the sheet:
CX1 = CX2 = 2(15pF - 2pF) = 26pF 22pF already in the bom
